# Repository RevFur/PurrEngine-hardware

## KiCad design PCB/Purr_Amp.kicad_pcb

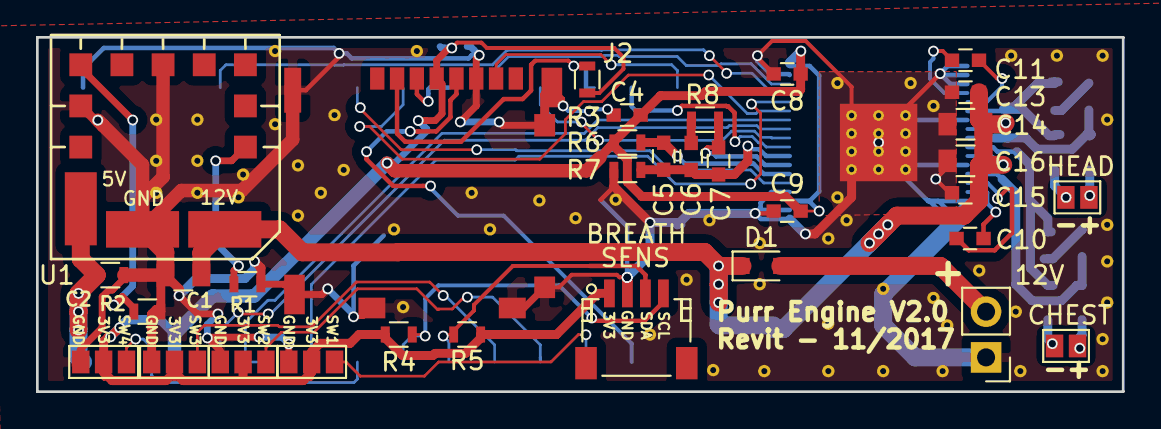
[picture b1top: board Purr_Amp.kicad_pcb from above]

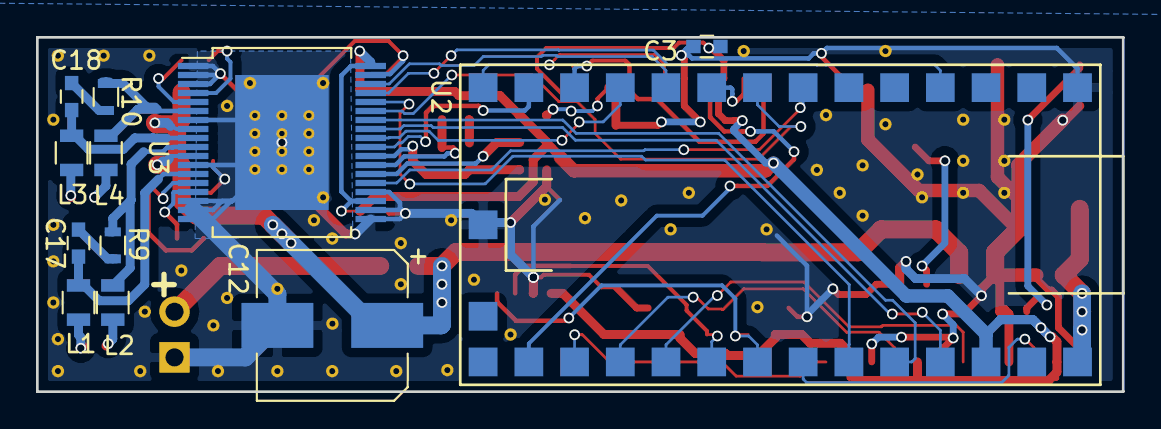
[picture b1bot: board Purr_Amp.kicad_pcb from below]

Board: 2 copper layers, 60.3 x 19.7 mm, 45 parts (12 on the bottom side), 44 nets.

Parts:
12V: 12V PWR; Pin_Header_Straight_1x02_Pitch2.54mm
BREATH: I2C_CONN; JST_SH_SM04B-SRSS-TB_04x1.00mm_Angled
C1: .33u; C_0805
C2: 100n; R_0603
C3, C4, C5, C8, C9, C10, C11, C13, C15, C17, C18: 100n; C_0603
C6: 4.7n; C_0603
C7: 680p; C_0603
C12: 47u 25V; CP_Elec_8x6.7
C14, C16: 1u; C_0805
CHEST: TRANSDUCER_A; GS2
D1: D; D_0805
HEAD: TRANSDUCER_B; GS2
J2: Micro_SD_Card; SDCard_Molex_5031821852
J4, J5, J6, J7: Conn_01x03; GS3
L1, L2, L3, L4: Bead; R_0805
R1, R6, R7: 0; R_0603
R2: 2.18K; R_0603
R3: 10K; R_0603
R4, R5: 2K2; R_0603
R8, R9, R10: 2.2K; R_0603
U1: OKL-T/1-W12N-C; MURATA_OKL1
U2: Teensy3.2; Teensy3.4_SMD
U3: STA333ML; ST_PowerSSO-36_SlugDown_ThermalVias

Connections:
+3V3: BREATH.1, C3.1, C4.1, C8.1, C9.2, J2.4, J4.2, J5.2, J6.2, J7.2, R3.1, R4.1, R5.1, R6.2, U2.31, U3.21, U3.36
+5V: C2.1, U1.4, U2.33
+12V: C1.1, C12.1, C13.2, C14.2, C15.2, C16.2, D1.1, U1.2, U3.8, U3.11
AUD_GAIN_SEL: U2.10, U3.34
AUD_INT: U2.28, U3.32
AUD_OVRSMP_SEL: U2.4, U3.33
AUD_PWRDN: U2.7, U3.23
AUD_RESET: U2.8, U3.31
GND: 12V.1, BREATH.2, C1.2, C2.2, C3.2, C4.2, C8.2, C9.1, C12.2, C13.1, C14.1, C15.1, C16.1, J2.6, J2.9, J4.3, J5.3, J6.3, J7.3, R1.2, R2.2, R7.2, U1.3, U1.7, U1.11, U2.1, U2.17, U3.1, U3.2, U3.3, U3.7, U3.12, U3.16, U3.17, U3.18, U3.19, U3.20, U3.22, U3.35, U3.37
I2C_SCL: BREATH.4, R4.2, U2.26
I2C_SDA: BREATH.3, R5.2, U2.25
I2S_BCLK: U2.11, U3.28
I2S_LRCLK: U2.30, U3.29
I2S_MCLK: U2.13, U3.27
I2S_TX: U2.29, U3.30
unnamed: C5.1, R6.1, U3.24
unnamed: C5.2, C6.2, C7.2, R7.1, U3.26
unnamed: C6.1, R8.2
unnamed: C7.1, R8.1, U3.25
unnamed: C10.1, U3.14
unnamed: C10.2, U3.15
unnamed: C11.1, U3.4
unnamed: C11.2, U3.5
unnamed: C17.1, L1.2, U3.13
unnamed: C17.2, R9.1
unnamed: C18.1, L3.2, U3.9
unnamed: C18.2, R10.1
unnamed: 12V.2, D1.2
unnamed: CHEST.1, L1.1
unnamed: CHEST.2, L2.1
unnamed: HEAD.1, L3.1
unnamed: HEAD.2, L4.1
unnamed: L2.2, R9.2, U3.10
unnamed: L4.2, R10.2, U3.6
unnamed: R1.1, U1.1
unnamed: R2.1, U1.6
SD_CLK: J2.5, U2.21
SD_CS: J2.2, R3.2, U2.12
SD_MISO: J2.7, U2.14
SD_MOSI: J2.3, U2.9
SW1: J4.1, U2.22
SW2: J5.1, U2.23
SW3: J6.1, U2.24
SW4: J7.1, U2.27

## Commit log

2018-11-15 Initial commit of hardware components
2018-11-15 Added .pdf version of Purr_Amp schematic
